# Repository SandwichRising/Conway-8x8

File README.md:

# Conway-8x8
8x8 Circuit Sculpture of Conway's Game of Life

   This project is the collection of files necessary to make the above pictured 8x8 grid sculpture playing out [Conway's Game of Life](https://www.youtube.com/watch?v=Kk2MH9O4pXY) on an ATmega 328P. This project spanned 3 separate periods: 110 hours were spent developing the original software and building a circuit sculpture for a [separate 6x6 design](./media/6x6_design.jpg) which maxed the CPU capabilities; 20 hours were spent doing a technical analysis, refactoring, and writeup of the created data structure to scale from 6x6 to larger sizes; 130 hours over 3 weeks were then spent developing this project into new physical hardware. 

   The 130-hour period is captured in this github. This time was spent integrating the new 8x8 software to match new hardware, conceptualizing the full physical design from scratch, modeling the wooden case in Fusion360, designing the circuit boards in KiCad, producing CNC gcode for the PCBs and case in Fusion360, cutting the wood and copper/fr4 circuit boards on an Onefinity CNC machine, treating the wood and creating epoxy lenses, soldering the circuits, as well as testing and improving the design while in-progress. The project was created to demonstrate hardware implementation of a data structure (from concept to physical object) for a classroom grade, as this process is much more complicated than a solely-software approach. Unfortunately, the project did not count for very much credit, however the entire process was quite therapeutic and educational, and I was very pleased with the results.

## What the Sculpture Does

   The sculpture creates a random gameboard using a floating microcontroller pin, and then applies Conway’s rules to evolve which cells live or die. The floating pin polls random energy in the air to seed the random number generator. The gameboard itself represents viewing one of an infinitely repeating 8x8 grid in every direction, as the top/bottom and left/right sides are considered ‘touching’ for the evolution process. Another way to visualize this is as a grid stretched over a [torus](https://en.wikipedia.org/wiki/Torus). This implementation remembers 48 board histories to check for duplicates, as a duplicate gameboard will always evolve along the same path (which traps the display into repeating itself forever). The bulk of the processor’s memory is used in saving these histories. If a duplicate gameboard is detected in history, the living cells flash out of existence in a specific way to let the observer know they ‘lived forever’, and a new random gameboard is generated. Otherwise, the game will continue to play out until all cells die out, and afterward a new board is generated. This 8x8 board has 68,719,476,736 unique starting conditions possible. 
  
  You can see the sculpture running in the video below. Unfortunately, the camera shutter speed clashes a bit with the FPS of the sculpture so the video footage doesn’t look as good as seeing it run in person. Lopsided ‘blinky’ math is used to transition cells on and off to make it easier for one's brain to track the groups of cells dying and coming alive each evolution cycle. The video was recorded while testing that the sculpture display matched what the software was providing, with an external Arduino streaming data to the display and the laptop simultaneously.

   I enjoy seeing the display run from behind the sculpture, where the LEDs can be seen through the circuit boards.

## The Project’s Goals
   The intent of the project had two primary purposes: refactor the existing software data structure to be more efficient, and to develop new improved techniques for hardware creation to realize the data structure physically. In software, a technical analysis of the original 6x6 data structure was done and improvements were made to allow up to a 32x32 size (while still maintaining auto-reset features to detect if a repeating pattern emerged). Methods for further improvement were also discovered, but not yet implemented. After the software was improved, an 8x8 size for the hardware was chosen for timeline practicality. In hardware, the goals were to create working SMD circuits using a CNC process, integrating multiple of these PCBs together into a larger overall circuit, designing this circuit alongside a tailor-cut housing to host them, and to attempt using epoxy as an appealing LED lens.
   
   The software was developed in Arduino IDE v1.8.13. [The source code is provided here](./src/conway3/conway3.ino).

## The Build Log
  The rest of this readme is designed as a build log. The build process is documented below for anyone wishing to recreate this sculpture. STL files for all housing pieces are located [here](./models), KiCad files for the circuit are provided [here](./kicad/conway), and images of the different PCB traces for an etching process are provided [here](./pcb_svg_images). Creating/providing gcode is outside the scope of this writeup, as the process is highly dependent on the specific tools used to manufacture.
  
   The housing is made from poplar wood, a light wood with a subtle natural greenish tint. The feet (and failed trim) are made from sapele, a naturally red wood. The wood and PCBs were all sealed with a polyurethane spray for protection. The circuits are all cut from single-sided copper fr4 PCB blanks. The CPU is a standalone ATmega 328P (flashed as a standalone chip using it's internal oscillator), 10k resistor (with yellow/blue shrink, to pull the reset pin up to 5v), and 10uF capacitor (seen on the rear, required for power smoothing). The LED PCBs use [74HC595 shift registers]( https://www.digikey.com/en/products/detail/nexperia-usa-inc/74HC595D-118/763087), [470 Ohm resistor arrays](https://www.digikey.com/en/products/detail/bourns-inc/CAY16-471J4LF/2566756), and generic green 3V 20mA LEDs. A generic USB PCB was soldered to the GND and 5V lines of the bus PCB (the 328P chip used does not support USB data, so only power was connected).

After developing the software, the circuits were drawn in KiCad (v5.1.9) to find the practical sizes and shapes for the circuit boards.

Once the circuits were designed and sized, electronic components were ordered and the wooden housing was modeled in Fusion360. After modeling, machine cutpaths were assigned and exported as gcode in Fusion360 and the back of the housing was cut. Wooden pillars were used to place the wood stock precisely on the CNC bed, as the board would need flipped on the next step, and the pillars allowed for exact X and Y axis alignment. Before cutting, a small amount of polyurethane was sprayed where the text engraving would be to prevent paint overspray from absorbing into the wood. After cutting, this engraving area was taped off and sprayed with black spray paint. After drying, sanding the area removed the excess paint but left the engraved text painted.

The wooden board was then flipped, aligned to the bed’s peg holes, and the front was then cut. The front used different woodworking bits to create the wavy pattern, cut away bulk material, engrave lettering, and drill LED holes. The same spray paint technique from before was used to fill the LIFE lettering with black paint (green epoxy was added later).

A process with two different types of epoxy was used for the visibile lenses over the leds. First, clear tape was placed over the display face, covering the LED holes, and a small amount of 2-part green epoxy was poured into the holes from behind. After the epoxy had time to set, the tape was removed and a different UV epoxy was added in a droplet-shape to create a magnifying lens over the top, then hardened with a UV light into its round shape. This picture shows the piece of scrap wood to test the process. Only one of the 5 test pours pictured has the UV lens over the top.

Additional trim was modeled and cut, with the plan to have more contrast in the design.

This did not work out as planned, though. The trim wood was cut to only be 3mm thick, but the board used was not perfectly flat and this resulted in a failed cut. Pre-processing the side of the board resting against the CNC machine bed flatter with a surfacing bit could have prevented this. There wasn’t enough sapele left in my shop to try again, so the contrasting trim idea was scrapped along with the failed cuts.  

Luckily, the section of sapele reserved for the feet was still usable, and this cut went well.

The LED PCBs were then cut on the CNC machine. The electrical traces are 0.7mm wide, and I had not cut this finely before. A total of 4 different styles of bits were used over multiple days before finding a 60-degree (inclusive) carbide bit that cut well at around 10k RPM, with some of the finer angled bits breaking in the process. More than 15 PCBs were cut, with 8 being usable in the end. You can see some of the progress from right to left in the picture.

Each PCB was hand soldered using a syringe of lead-free low temperature solder on the SMD parts, and lead-free spooled solder on the through-hole parts. The soldering was done with a combination of hot air reflow and soldering iron work until all connections tested correctly with a multimeter. 

The LED PCBs were then assembled using the bus PCB to connect them all, and then brain PCB was attached using solid-core wire (to create a floating effect) and a thin data wire was run to the data-in of the first LED PCB. All the data-out/data-in ports on the LED PCBs were then connected using solid core wire along the side of the structure. The USB port was also connected to the bus PCB, but only 5v and GND were connected to the USB port. 

The display was tested during assembly by streaming data from an Arduino UNO (with a 328P processor) using jumper wires, making sure the display matched up with what the software was outputting to the laptop over serial connection (shown in a video above). After the testing was verified and the circuit was fully assembled, the copper was sprayed with polyurethane to protect it from moisture.

After all testing was done, a standalone 328P was flashed with the 8x8 program (using the internal oscillator instead of external clock) and the circuit was attached to the housing with screws. The view from the rear while its running is still my favorite.

If you’ve made it this far, extra thanks for taking a look! If you make one, be sure to let me know!

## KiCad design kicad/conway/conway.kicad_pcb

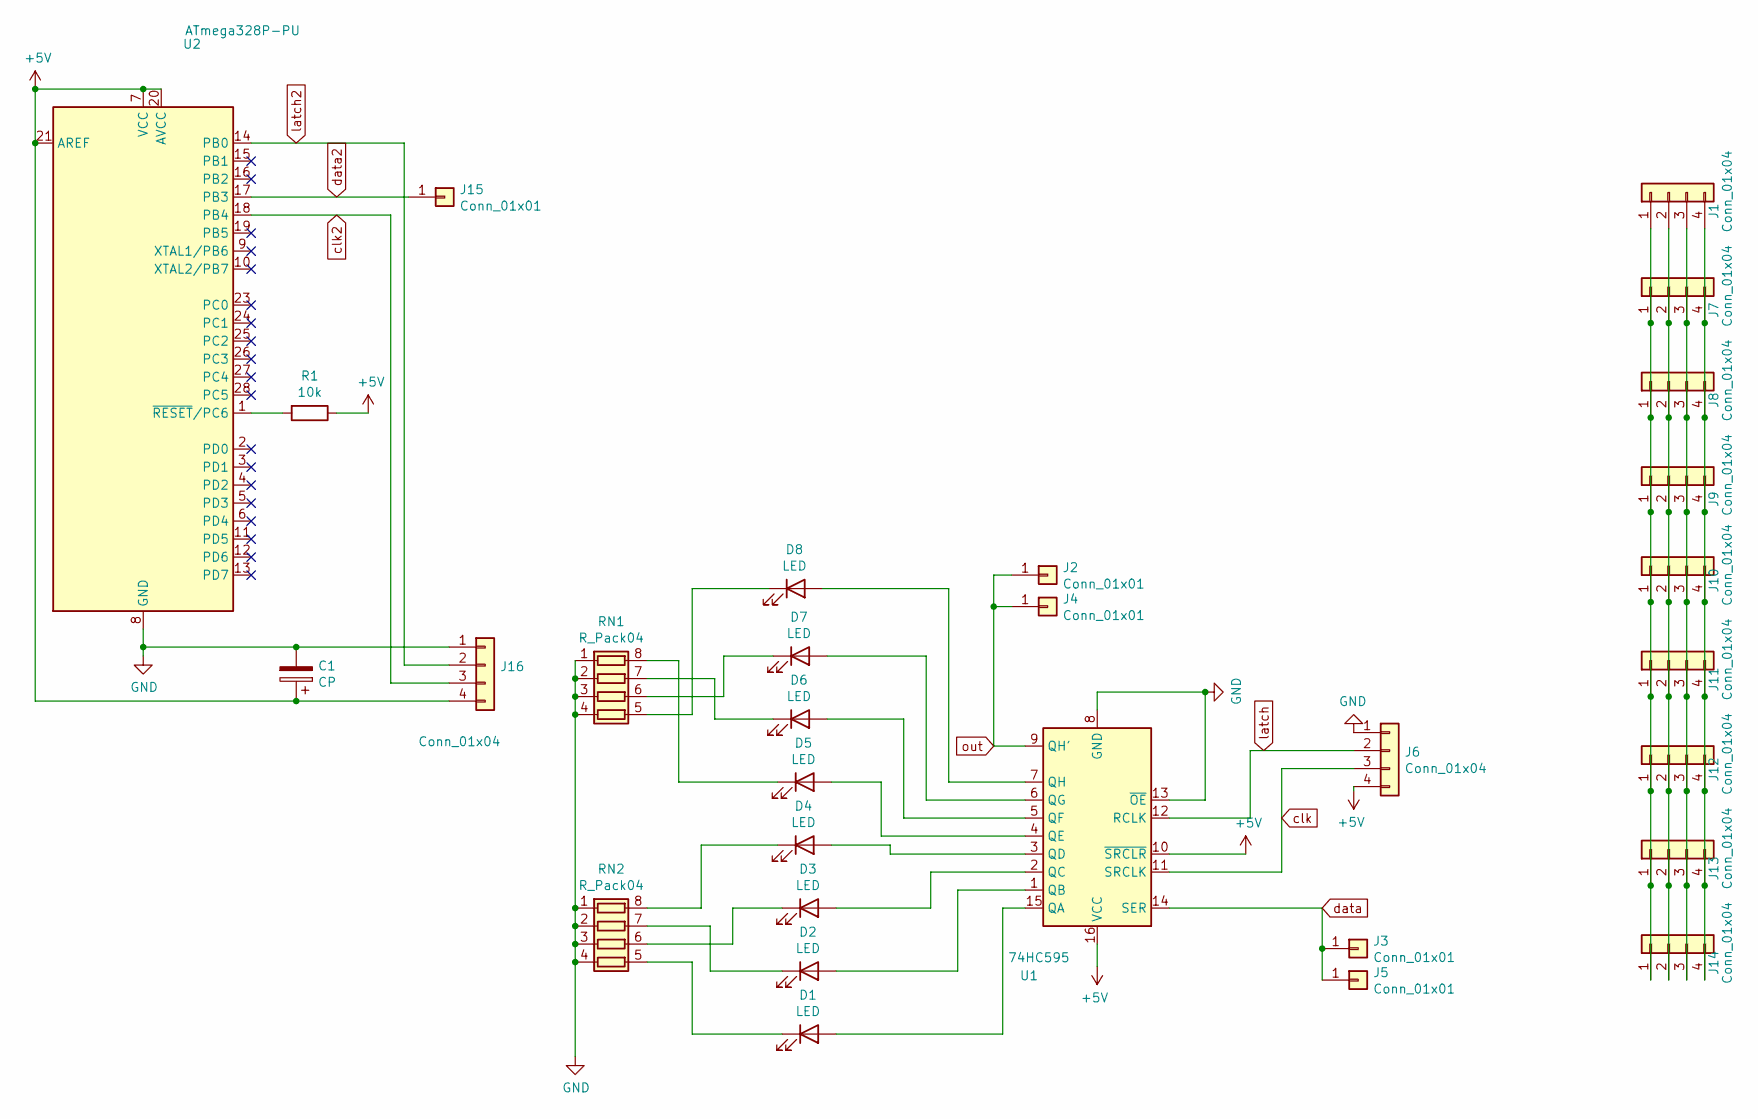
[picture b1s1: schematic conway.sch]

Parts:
C1: CP; CP_Radial_D5.0mm_P2.50mm_Custom_HandSolder
D1, D2, D3, D4, D5, D6, D7, D8: LED; PinHeader_1x02_P2.54mm_Vertical_Custom_Hand_Solder
J1, J6, J7, J8, J9, J10, J11, J12, J13, J14, J16: Conn_01x04; PinHeader_1x04_P2.54mm_Vertical_Custom_Hand_Solder
J2, J5, J15: Conn_01x01; PinHeader_1x01_P2.54mm_Vertical_Custom_Left_Hand_Solder
J3, J4: Conn_01x01; PinHeader_1x01_P2.54mm_Vertical_Custom_Right_Hand_Solder
R1: 10k; R_Axial_DIN0207_L6.3mm_D2.5mm_P7.62mm_Horizontal_Custom_Han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
RN1, RN2: R_Pack04; R_Array_Convex_4x0603_Custom_Hand_Solder
U1: 74HC595; SOIC-16_3.9x9.9mm_P1.27mm_Custom_Hand_Solder
U2: ATmega328P-PU; DIP-28_W7.62mm_Custom_HandSolder

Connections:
+5V: C1.1, J6.4, J16.4, R1.1, U1.10 (~SRCLR), U1.16 (VCC), U2.7 (VCC), U2.20 (AVCC), U2.21 (AREF)
GND: C1.2, J6.1, J16.1, RN1.1 (R1.1), RN1.2 (R2.1), RN1.3 (R3.1), RN1.4 (R4.1), RN2.1 (R1.1), RN2.2 (R2.1), RN2.3 (R3.1), RN2.4 (R4.1), U1.8 (GND), U1.13 (~OE), U2.8 (GND), U2.22 (GND)
unnamed: D1.1 (K), RN2.5 (R4.2)
unnamed: D1.2 (A), U1.15 (QA)
unnamed: D2.1 (K), RN2.7 (R2.2)
unnamed: D2.2 (A), U1.1 (QB)
unnamed: D3.1 (K), RN2.6 (R3.2)
unnamed: D3.2 (A), U1.2 (QC)
unnamed: D4.1 (K), RN2.8 (R1.2)
unnamed: D4.2 (A), U1.3 (QD)
unnamed: D5.1 (K), RN1.8 (R1.2)
unnamed: D5.2 (A), U1.4 (QE)
unnamed: D6.1 (K), RN1.7 (R2.2)
unnamed: D6.2 (A), U1.5 (QF)
unnamed: D7.1 (K), RN1.6 (R3.2)
unnamed: D7.2 (A), U1.6 (QG)
unnamed: D8.1 (K), RN1.5 (R4.2)
unnamed: D8.2 (A), U1.7 (QH)
unnamed: J1.1, J7.1, J8.1, J9.1, J10.1, J11.1, J12.1, J13.1, J14.1
unnamed: J1.2, J7.2, J8.2, J9.2, J10.2, J11.2, J12.2, J13.2, J14.2
unnamed: J1.3, J7.3, J8.3, J9.3, J10.3, J11.3, J12.3, J13.3, J14.3
unnamed: J1.4, J7.4, J8.4, J9.4, J10.4, J11.4, J12.4, J13.4, J14.4
unnamed: R1.2, U2.1 (~RESET~/PC6)
clk: J6.3, U1.11 (SRCLK)
clk2: J16.3, U2.18 (PB4)
data: J3.1, J5.1, U1.14 (SER)
data2: J15.1, U2.17 (PB3)
latch: J6.2, U1.12 (RCLK)
latch2: J16.2, U2.14 (PB0)
out: J2.1, J4.1, U1.9 (QH')

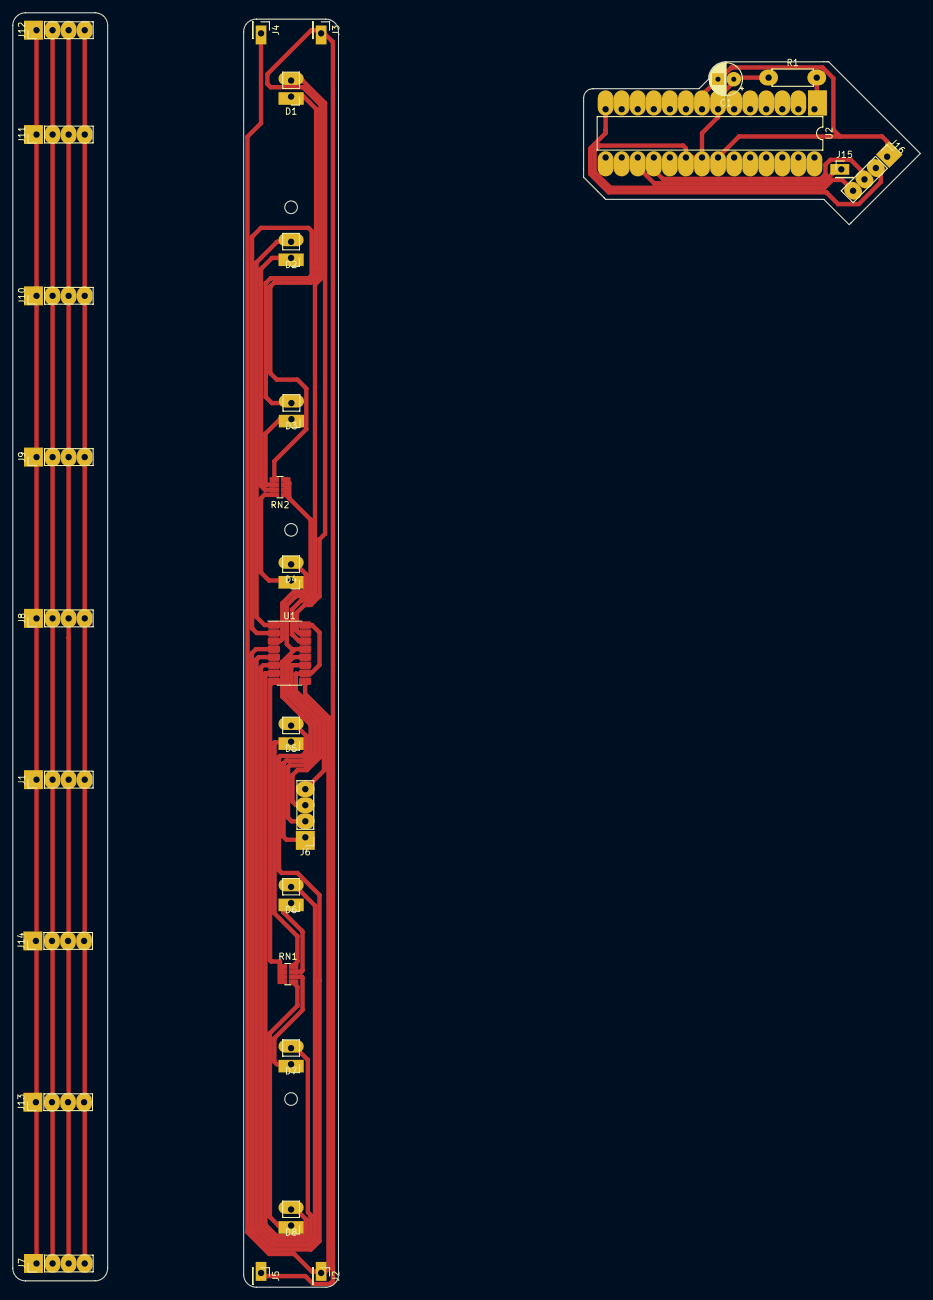
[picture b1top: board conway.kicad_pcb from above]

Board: 2 copper layers, 143.5 x 201.5 mm, 30 parts (0 on the bottom side), 30 nets.

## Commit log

2023-08-17 Update README.md
    Begin readme
2023-08-18 import all assets
2023-08-18 readme formatting
2023-08-18 change to gif format videos
2023-08-18 correcting typo
2023-08-18 correcting typo 2
2023-08-18 cleanup
